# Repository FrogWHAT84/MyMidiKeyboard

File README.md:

# MyMidiKeyboard
This is MiDi keyboard based on Kai pereira's starter project (https://github.com/KaiPereira/MIDI-Keypad/ project).

It is based on Waveshare ESP32-S3-Zero microcontroller, has capacitive touch panels, EC11 rotary encoder, Kailh Choc Low-Profile Switches, Bourns Slide Potentiometers and a SK6812 MINI-E Neopixels. it is meqant to be used with pc in apps such as FL studio.
As a firmware you can use KMK (https://github.com/KMKfw/kmk_firmware/blob/main/docs/en/Getting_Started.md)

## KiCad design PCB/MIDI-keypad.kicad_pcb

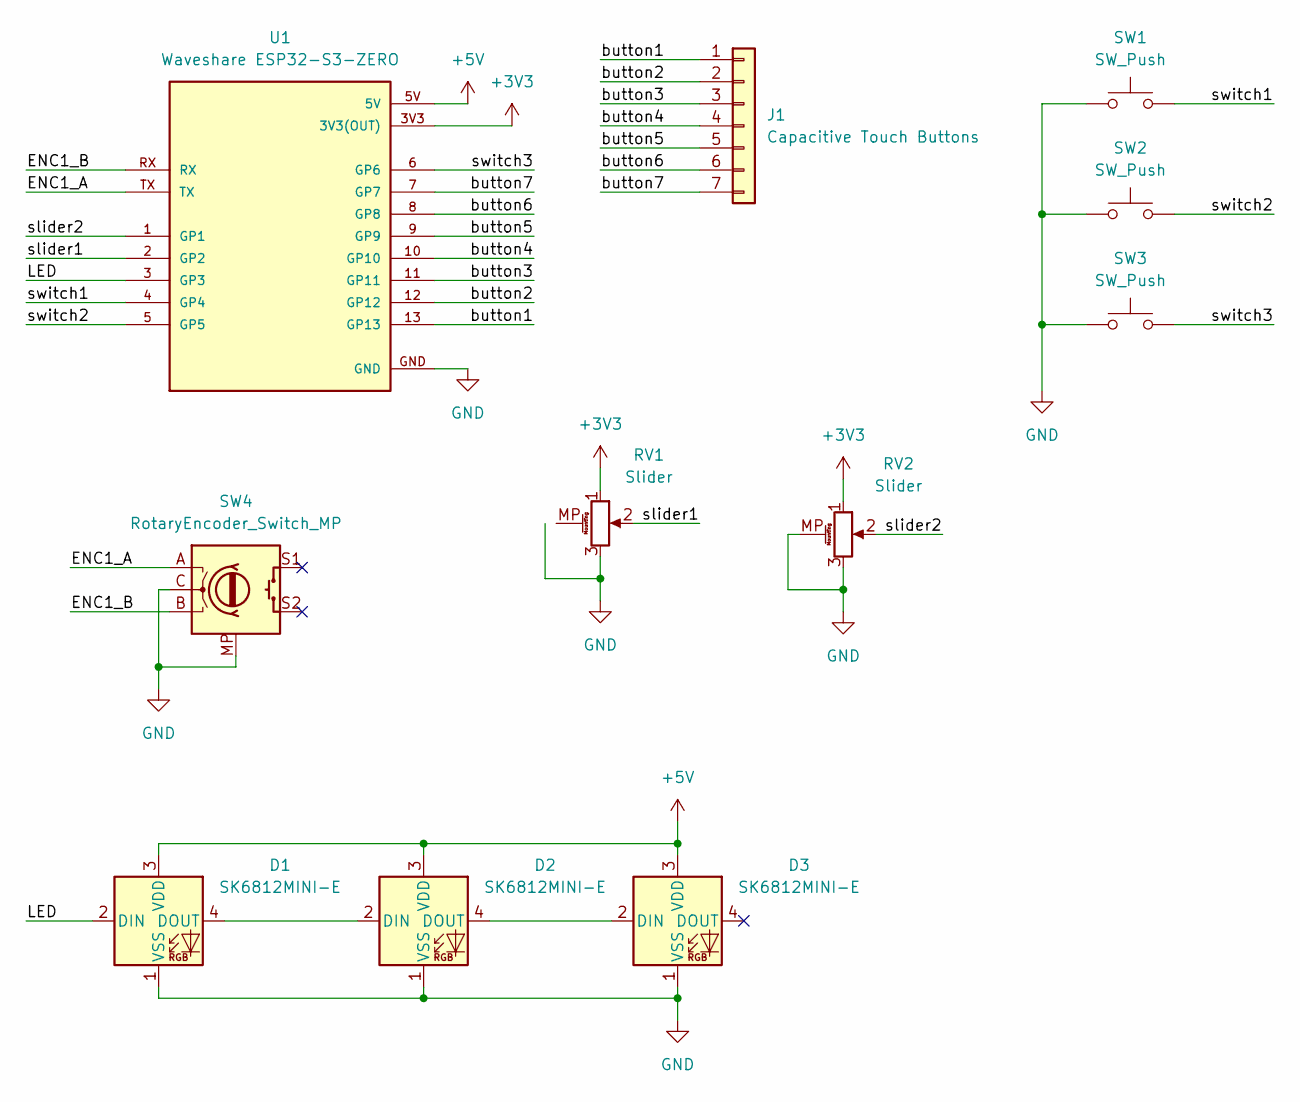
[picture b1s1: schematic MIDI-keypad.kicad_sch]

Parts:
D1, D2, D3: SK6812MINI-E; LED_SK6812MINI-E_3.2x2.8mm_P1.5mm_ReverseMount
J1: Capacitive Touch Buttons; Capacitive Keys
RV1, RV2: Slider; Potentiometer_Bourns_PTA1543_Single_Slide
SW1, SW2, SW3: SW_Push; Kailh Choc Low-Profile Switches
SW4: RotaryEncoder_Switch_MP; RotaryEncoder_Alps_EC11E-Switch_Vertical_H20mm
U1: Waveshare ESP32-S3-ZERO; Waveshare ESP32-S3-Zero; PARTREV NA

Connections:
+3V3: RV1.1, RV2.1, U1.3V3 (3V3(OUT))
+5V: D1.3 (VDD), D2.3 (VDD), D3.3 (VDD), U1.5V
/ENC1_A: SW4.A, U1.TX
/ENC1_B: SW4.B, U1.RX
/LED: D1.2 (DIN), U1.3 (GP3)
/button1: J1.1, U1.13 (GP13)
/button2: J1.2, U1.12 (GP12)
/button3: J1.3, U1.11 (GP11)
/button4: J1.4, U1.10 (GP10)
/button5: J1.5, U1.9 (GP9)
/button6: J1.6, U1.8 (GP8)
/button7: J1.7, U1.7 (GP7)
/slider1: RV1.2, U1.2 (GP2)
/slider2: RV2.2, U1.1 (GP1)
/switch1: SW1.2, U1.4 (GP4)
/switch2: SW2.2, U1.5 (GP5)
/switch3: SW3.2, U1.6 (GP6)
GND: D1.1 (VSS), D2.1 (VSS), D3.1 (VSS), RV1.3, RV2.3, RV2.MP (MountPin), SW1.1, SW2.1, SW3.1, SW4.C, SW4.MP, U1.GND
unnamed: D1.4 (DOUT), D2.2 (DIN)
unnamed: D2.4 (DOUT), D3.2 (DIN)

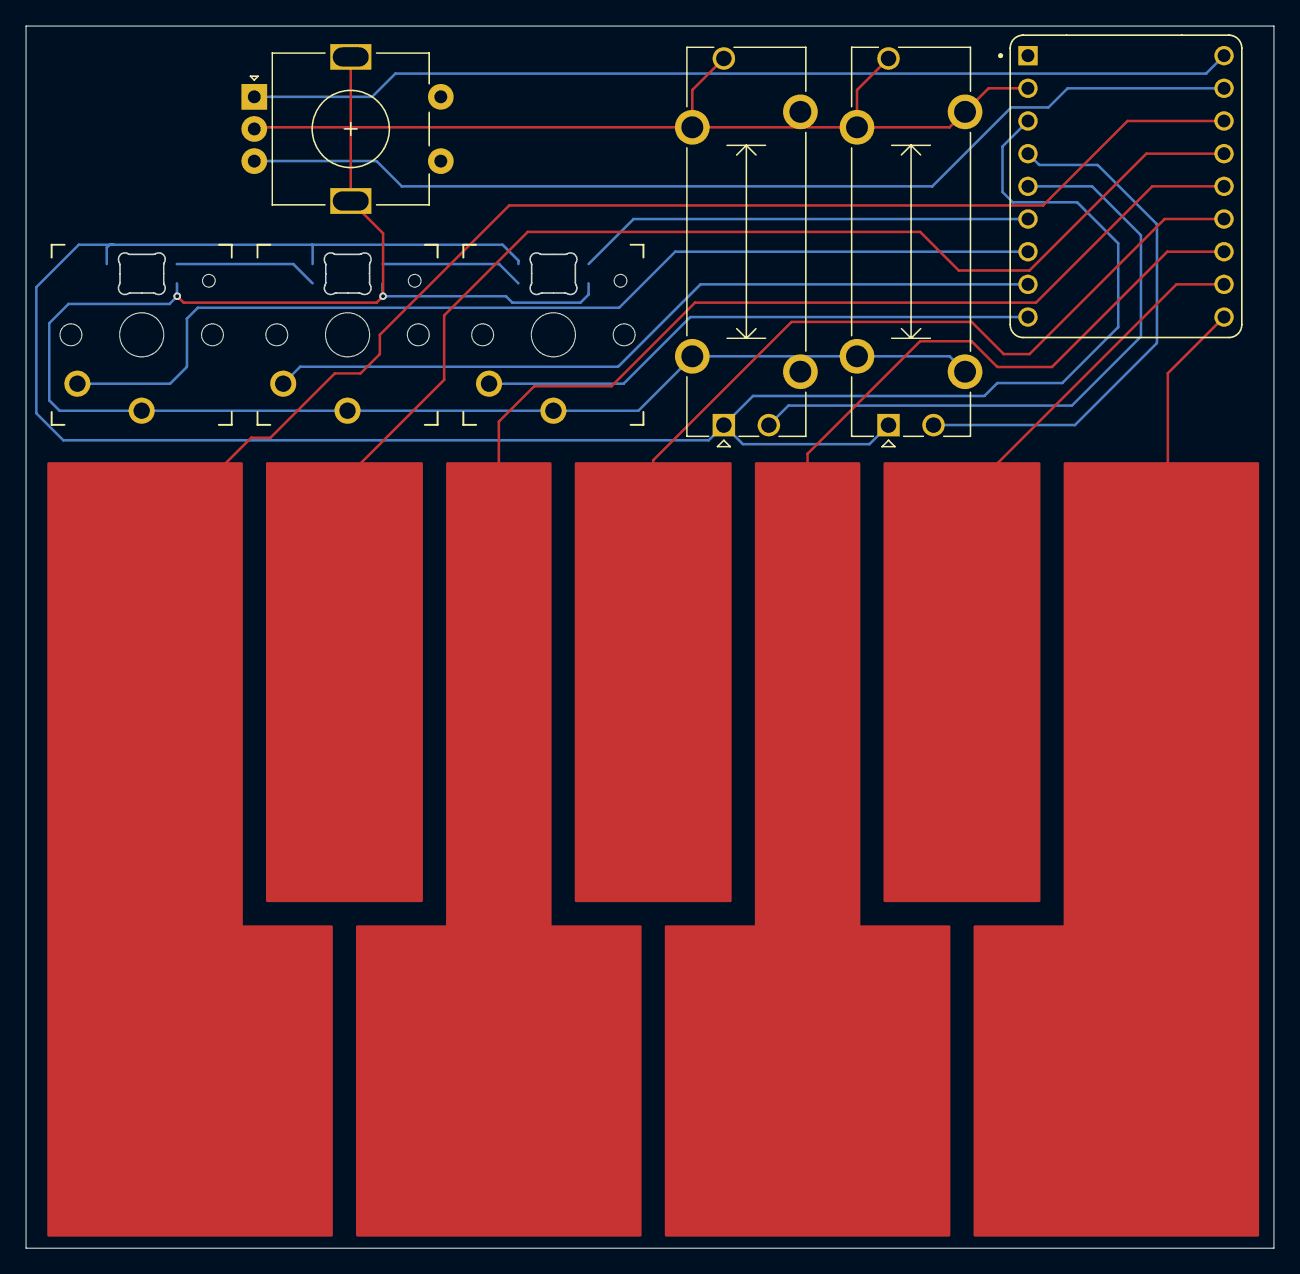
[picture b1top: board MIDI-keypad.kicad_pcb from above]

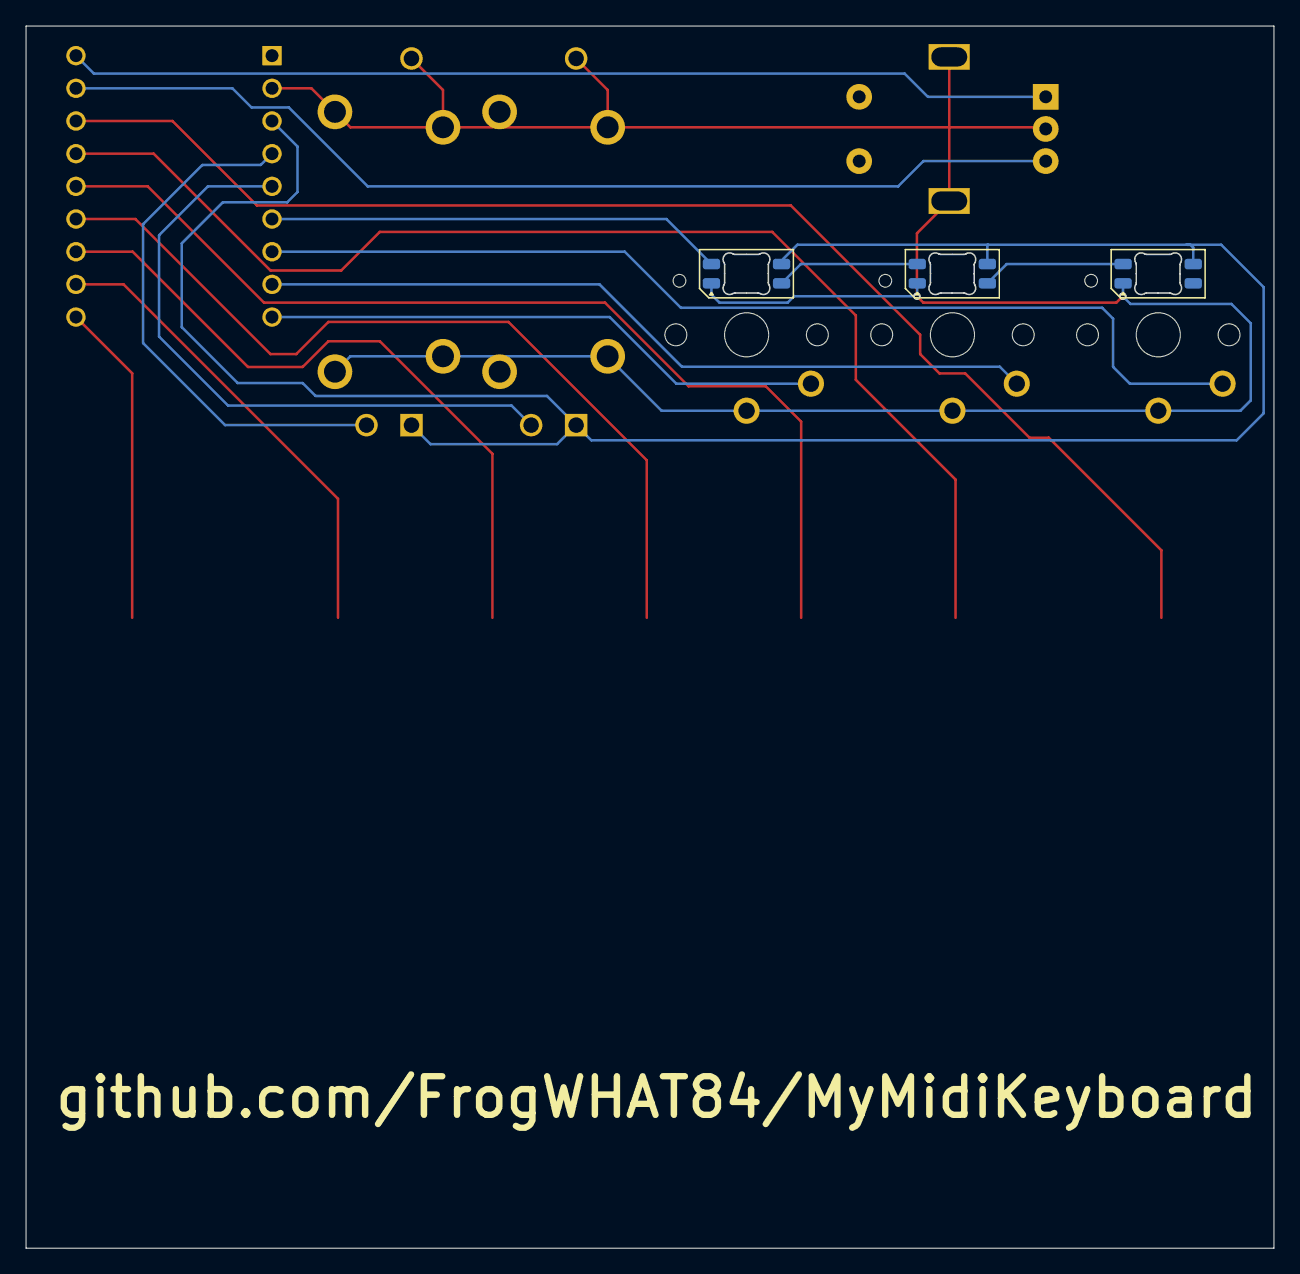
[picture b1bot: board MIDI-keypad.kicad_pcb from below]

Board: 2 copper layers, 97.0 x 95.0 mm, 11 parts (3 on the bottom side), 20 nets.
